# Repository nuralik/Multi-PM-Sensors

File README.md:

# A smart mobile platform for air quality monitoring

The dynamics of urban particulate matter (PM) is complicated by the large number of PM micro-sources that are spatially and temporally non-uniformly distributed.  Any effort to understand this dynamics and make policies to improve air quality requires the identification of these micro-sources and their complete characterization.  Such an identification/characterization of PM sources is only possible if air quality monitoring is made at high enough spatial and temporal resolution.  Large-scale air quality monitoring, requires networked sensors that are low-cost and compact in size while also being accurate and appropriately sensitive.  With increasing availability of low-cost sensors, large-scale monitoring maybe possible if their measurement accuracy and sensitivity is established under field conditions.  As part of this project, a network-ready platform that can house multiple sensors will be deployed in a pilot study to demonstrate the possibility of making large-scale measurements with commercial low-cost sensors.

## Particle sensors used in this project

* Shinyei ppd42ns

* Samyoung dsm501a

* Plantower PMS5003

* Honeywell hpma115s0

* [Potsdam Sensors](https://www.potsdamsensors.com/) MEAS

## Code 
[Arduino Code](https://github.com/nuralik/Multi-PM-Sensors/blob/master/Arduino_Code/PM_sensors.ino)

[Data Analysis](https://github.com/nuralik/A-smart-mobile-platform-for-air-quality-monitoring/blob/master/NACL%20TEST%20(1).ipynb)

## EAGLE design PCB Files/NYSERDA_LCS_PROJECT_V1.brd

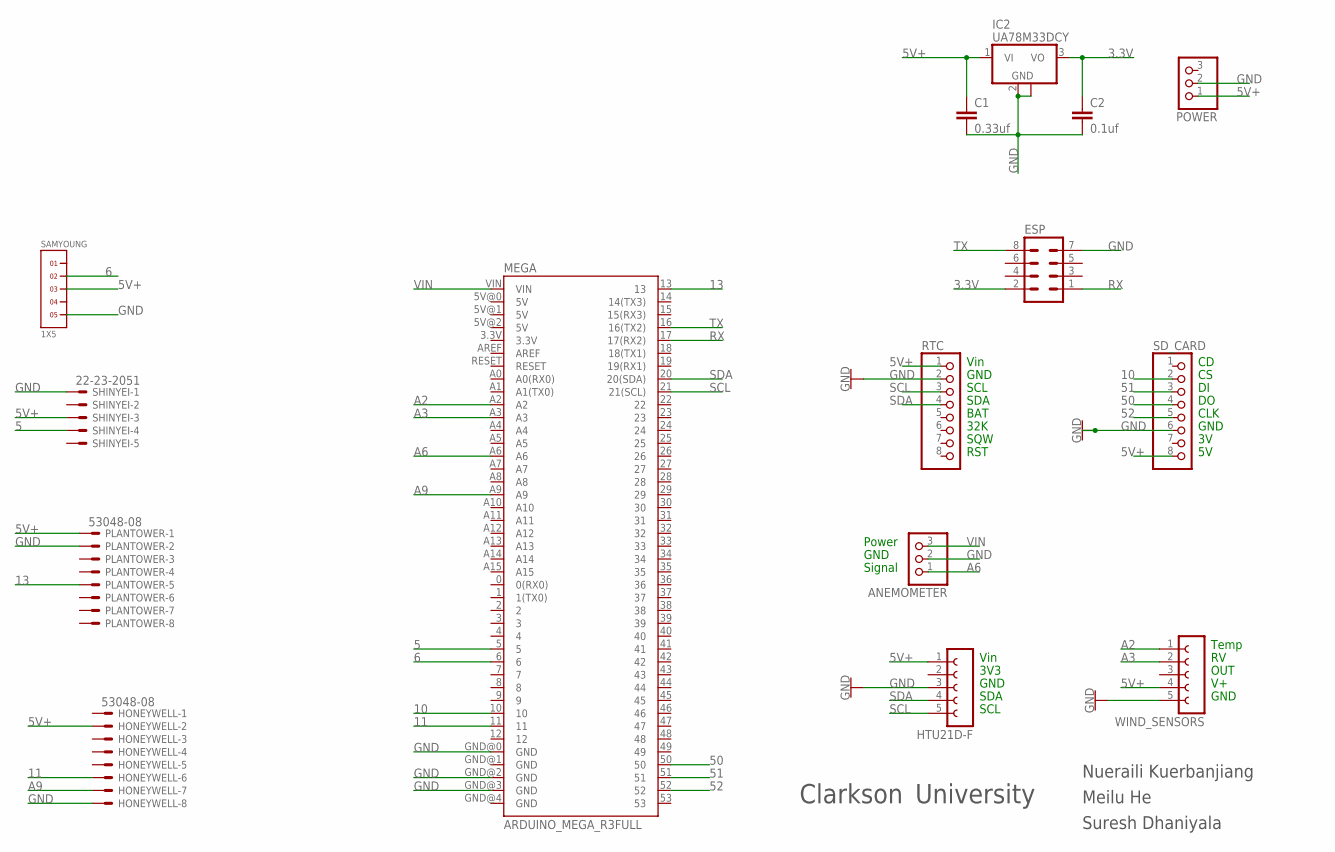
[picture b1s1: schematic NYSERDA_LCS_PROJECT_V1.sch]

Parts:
ANEMOMETER: PINHD-1X3; 1X03
C1: 0.33uf; C2.5-2
C2: 0.1uf; C2.5-2
ESP: MA04-2
HONEYWELL: 53048-08
HTU21D-F: FE05-1
IC2: UA78M33DCY; SOT223
MEGA: ARDUINO_MEGA_R3FULL; ARDUINO_MEGA
PLANTOWER: 53048-08
POWER: PINHD-1X3; 1X03
RTC: PINHD-1X8BIG; 1X08-BIG
SAMYOUNG: 1X5
SD_CARD: PINHD-1X8BIG; 1X08-BIG
SHINYEI: 22-23-2051
WIND_SENSORS: FE05-1

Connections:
3.3V: C2.1, ESP.2, IC2.3 (VO)
5: MEGA.5, SHINYEI.4
5V+: C1.1, HONEYWELL.2, HTU21D-F.1, IC2.1 (VI), PLANTOWER.1, POWER.1, RTC.1, SAMYOUNG.3, SD_CARD.8, SHINYEI.3, WIND_SENSORS.4
6: MEGA.6, SAMYOUNG.2
10: MEGA.10, SD_CARD.2
11: HONEYWELL.6, MEGA.11
13: MEGA.13, PLANTOWER.5
50: MEGA.50, SD_CARD.4
51: MEGA.51, SD_CARD.3
52: MEGA.52, SD_CARD.5
A2: MEGA.A2, WIND_SENSORS.1
A3: MEGA.A3, WIND_SENSORS.2
A6: ANEMOMETER.1, MEGA.A6
A9: HONEYWELL.7, MEGA.A9
GND: ANEMOMETER.2, C1.2, C2.2, ESP.7, HONEYWELL.8, HTU21D-F.3, IC2.2 (GND), IC2.4 (GND), MEGA.GND@0 (GND), MEGA.GND@2 (GND), MEGA.GND@3 (GND), PLANTOWER.2, POWER.2, RTC.2, SAMYOUNG.5, SD_CARD.6, SHINYEI.1, WIND_SENSORS.5
RX: ESP.1, MEGA.17 (17(RX2))
SCL: HTU21D-F.5, MEGA.21 (21(SCL)), RTC.3
SDA: HTU21D-F.4, MEGA.20 (20(SDA)), RTC.4
TX: ESP.8, MEGA.16 (16(TX2))
VIN: ANEMOMETER.3, MEGA.VIN

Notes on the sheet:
Temp
OUT
GND
CLK
Vin
3V3
SDA
SCL
BAT
32K
SQW
RST
Signal
Power
Clarkson
University
Nueraili Kuerbanjiang
Meilu He
Suresh Dhaniyala

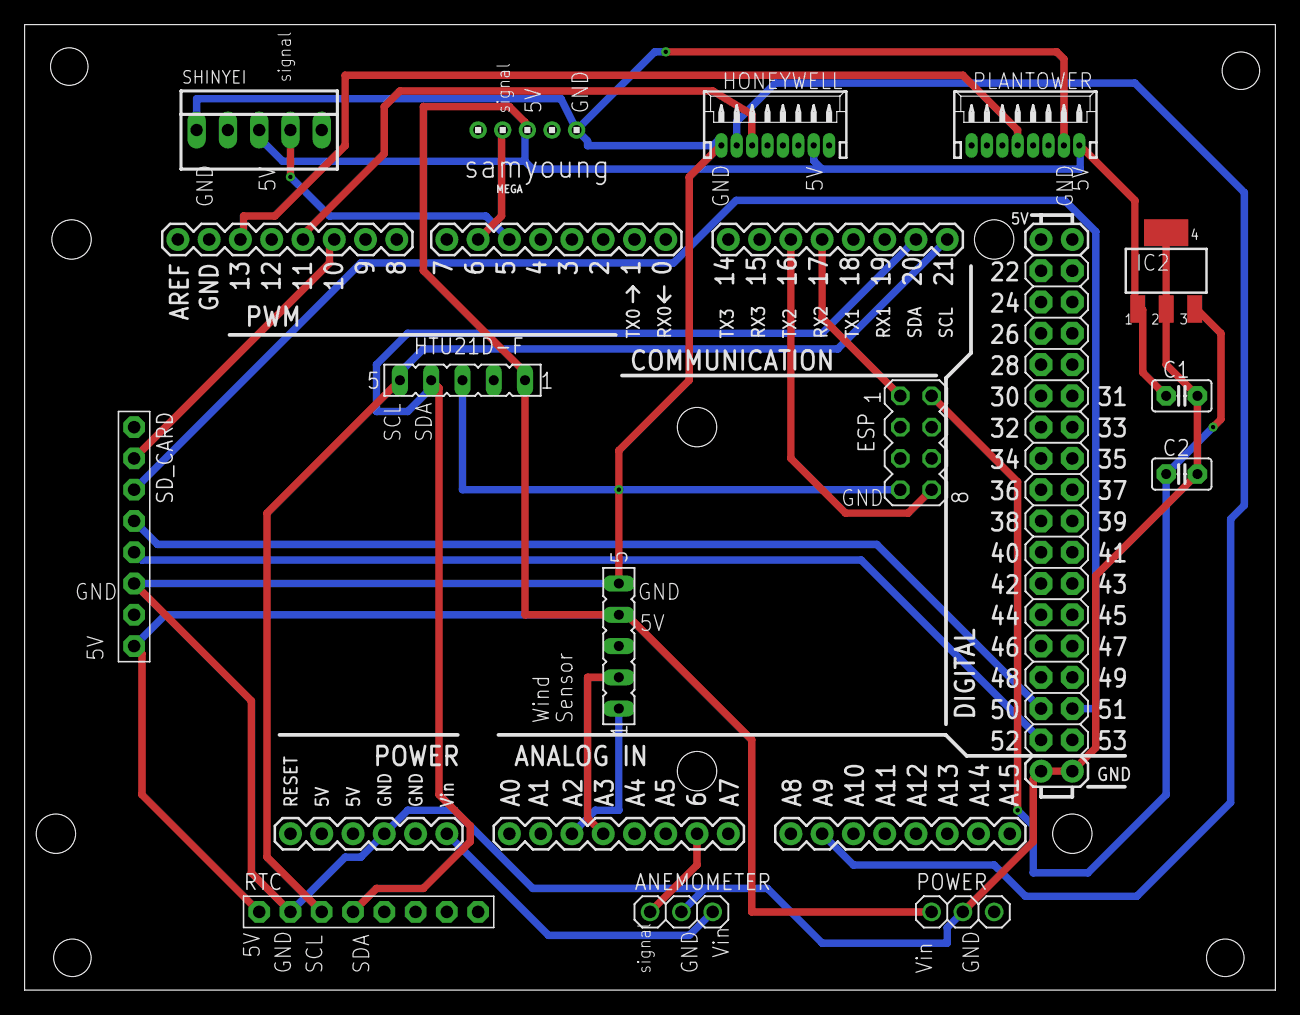
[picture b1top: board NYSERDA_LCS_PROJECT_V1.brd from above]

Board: 2 copper layers, 101.6 x 78.4 mm, 15 parts (0 on the bottom side), 20 nets.

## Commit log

2018-06-12 Create LICENSE
2018-06-12 Update LICENSE
2018-07-01 Data Analysing
2018-07-01 Create Data Analysing
2018-07-01 data
2018-07-01 Create Windtunnel
2018-07-05 Added New test Text file
2018-07-12 Uploaded PCB File
2018-07-13 Arduino Code
2018-07-15 Set theme jekyll-theme-slate
2018-07-15 Set theme jekyll-theme-midnight
2018-07-15 Set theme jekyll-theme-architect
2018-09-08 Random_Forest
2018-09-08 SVM(R)_
2018-10-26 Set theme jekyll-theme-cayman
2018-10-26 Create CNAME

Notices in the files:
parts and their libraries:
SparkFun-Boards: Licensing: Creative Commons ShareAlike 4.0 International - https://creativecommons.org/licenses/by-sa/4.0
